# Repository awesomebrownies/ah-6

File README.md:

# ah-6
AH-6 Little Bird: glow-in-the-dark circuit keychain

It uses transistors and glows in the dark. The brightness of the LED's can be adjusted using a potentiometer. I've wired it up to also use a capacitor to prolong LED life.

## Schematic

## PCB

## 3D Model

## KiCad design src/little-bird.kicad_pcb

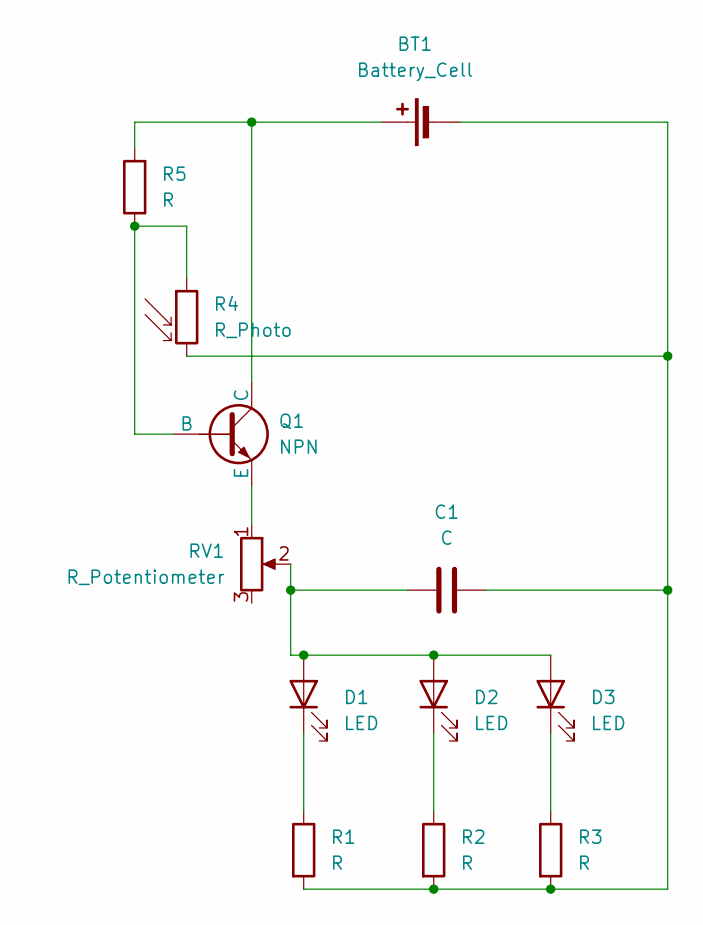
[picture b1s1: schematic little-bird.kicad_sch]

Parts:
BT1: Battery_Cell; BatteryHolder_Keystone_3034_1x20mm
C1: C; CP_Radial_D8.0mm_P5.00mm
D1, D2, D3: LED; LED_D5.0mm
Q1: NPN; TO-92L_HandSolder
R1, R2, R3, R5: R; R_Axial_DIN0207_L6.3mm_D2.5mm_P7.62mm_Horizontal
R4: R_Photo; R_LDR_5.1x4.3mm_P3.4mm_Vertical
RV1: R_Potentiometer; Potentiometer_Vishay_T73YP_Vertical

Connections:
unnamed: BT1.1 (+), Q1.1 (C), R5.2
unnamed: BT1.2 (-), C1.2, R1.2, R2.2, R3.2, R4.2
unnamed: C1.1, D1.2 (A), D2.2 (A), D3.2 (A), RV1.2
unnamed: D1.1 (K), R1.1
unnamed: D2.1 (K), R2.1
unnamed: D3.1 (K), R3.1
unnamed: Q1.2 (B), R4.1, R5.1
unnamed: Q1.3 (E), RV1.1

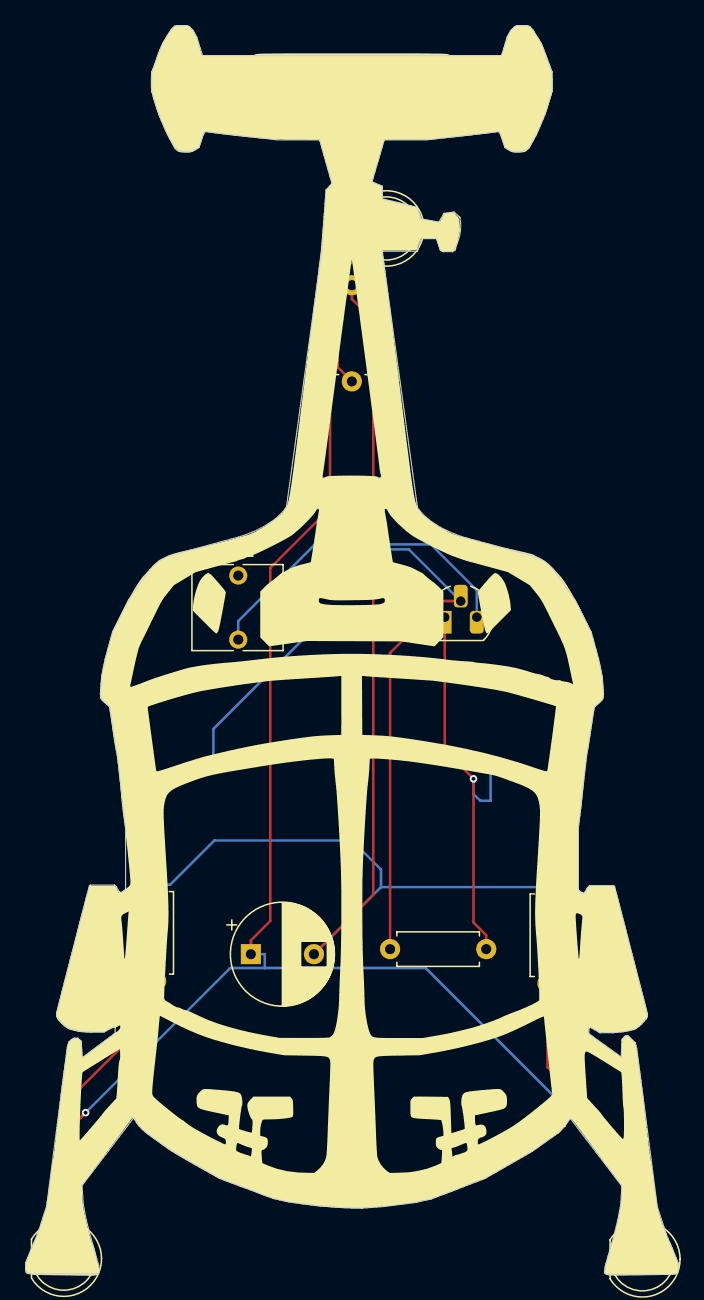
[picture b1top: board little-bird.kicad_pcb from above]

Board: 2 copper layers, 51.7 x 99.0 mm, 12 parts (1 on the bottom side), 8 nets.

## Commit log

2025-05-18 Add pcb files
2025-05-18 Update PCB
